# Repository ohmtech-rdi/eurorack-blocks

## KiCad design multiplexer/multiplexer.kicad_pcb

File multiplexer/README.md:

# multiplexer

## Description

This block allows to multiplex up to 8 `pot` or `trim` values into a single value.
Its design is detailed [here](./documentation/design.md).

## Overview

The number of actual Analog GPIOs on an MCU is always very limited, and one can quickly
have more controls and CVs on their panel than the number of available Analog GPIOs.

Multiplexing multiple signals to one signal allows to overcome this problem, at the expense
of a slower reading rate. Therefore it is suited for slowly varying signals such as the ones
delivered by a potentiometer.

This block provides up to 8 signals multiplexing. Reading a particular input is done
by putting the address of the input as a number expressed in binary.

Since 1 Analog GPIO is needed for the signal, 3 General GPIOs for the address, to reach a total
of 8 inputs, when a traditional MCU has far more General GPIOs than analog GPIOs.

Multiple `multiplexer` can be used, for example for a module with 8 parameters,
one `multiplexer` for the 8 `pot`, and another for the 8 attenuverter `trim`.
In that case, note that the same 3 GPIO outputs address can be reused for both multiplexers.

## Connecting

- This block needs its `GND` to be connected to the ground. All `GND` pins are connected
   internally,
- This block needs its `3V3A` to be connected to the Daisy Seed 3V3 Analog Power I/O on Pin 21,
- The signal `OUT` is the multiplexer output. It should be connected to any Analog GPIO of the
   target MCU. See [Daisy Seed pinout](https://images.squarespace-cdn.com/content/v1/58d03fdc1b10e3bf442567b8/1591827747342-HCXMM2NNR26SP5F4U2CJ/ke17ZwdGBToddI8pDm48kN5PbQBGNYbW-5Hm1pf8hRF7gQa3H78H3Y0txjaiv_0fDoOvxcdMmMKkDsyUqMSsMWxHk725yiiHCCLfrh8O1z4YTzHvnKhyp6Da-NYroOW3ZGjoBKy3azqku80C789l0kLp48N9LluBiCpBrPZntaz462IffsVrAff3VJkwKncM1HZuDnV98dfxM9yHlqFkUQ/DaisyPinoutRev4%404x.png?format=500w) for details.
- The signals from `IN0` to `IN7` are the inputs signals which would typically be connected to
   a `pot` or `trim` block `OUT`.

## Using

```c++
int main ()
{
   using namespace erb;
   
   Module module;
   Multiplexer mux (
      module, AdcPin6,              // 1.
      Pin23, Pin24, Pin25           // 2.
   );
   
   module.run ([&](){
      for (size_t i = 0 ; i < 8 ; ++i)
      {
         float pot_value = mux [i]; // 3.
      }
   });
}
```

1. Attach the multiplexer to the module and specify the same analog pin
   as the one used for connecting,
2. And specify the same digitals pins as the one used for connecting,
3. Retrieve the normalized (in the `0.f` to `1.f` range) floating-point pot value
   for input `IN` number `i`.

The `Multiplexer` class reference is available [here](./documentation/reference.md).

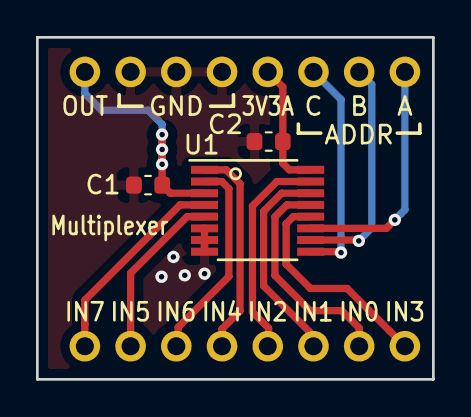
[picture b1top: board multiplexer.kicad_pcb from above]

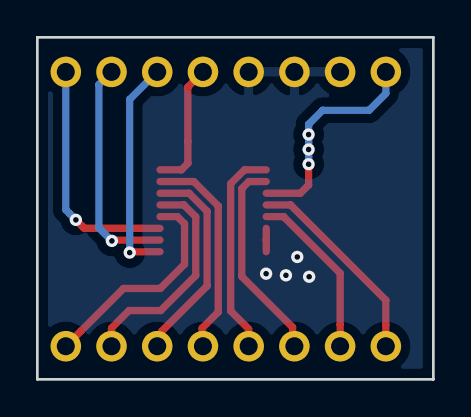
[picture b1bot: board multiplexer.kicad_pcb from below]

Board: 2 copper layers, 22.0 x 19.0 mm, 5 parts (2 on the bottom side), 14 nets.

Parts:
C1: 1n; C_0603_1608Metric
C2: 100n; C_0603_1608Metric
J2: BOTTOM; PinHeader_1x08_P2.54mm_Vertical
J3: TOP; PinHeader_1x08_P2.54mm_Vertical
U1: 4051; TSSOP-16_4.4x5mm_P0.65mm

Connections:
+3V3: C2.2, J3.5, U1.16
ADDR_0: J3.8, U1.11
ADDR_1: J3.7, U1.10
ADDR_2: J3.6, U1.9
GND: C1.2, C2.1, J3.2, J3.3, J3.4, U1.6, U1.7, U1.8
IN0: J2.7, U1.13
IN1: J2.6, U1.14
IN2: J2.5, U1.15
IN3: J2.8, U1.12
IN4: J2.4, U1.1
IN5: J2.2, U1.5
IN6: J2.3, U1.2
IN7: J2.1, U1.4
OUT: C1.1, J3.1, U1.3

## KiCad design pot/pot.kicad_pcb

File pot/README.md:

# pot

## Description

This block is a simple potentiometer.
Its design is detailed [here](./documentation/design.md).

## Connecting

- This block needs its `GND` to be connected to the ground. All `GND` pins are connected
   internally,
- This block needs its `3V3A` to be connected to the Daisy Seed 3V3 Analog Power I/O on Pin 21,
- The signal `OUT` is the potentiometer value. It should be connected to any Analog GPIO of the
   target MCU. See [Daisy Seed pinout](https://images.squarespace-cdn.com/content/v1/58d03fdc1b10e3bf442567b8/1591827747342-HCXMM2NNR26SP5F4U2CJ/ke17ZwdGBToddI8pDm48kN5PbQBGNYbW-5Hm1pf8hRF7gQa3H78H3Y0txjaiv_0fDoOvxcdMmMKkDsyUqMSsMWxHk725yiiHCCLfrh8O1z4YTzHvnKhyp6Da-NYroOW3ZGjoBKy3azqku80C789l0kLp48N9LluBiCpBrPZntaz462IffsVrAff3VJkwKncM1HZuDnV98dfxM9yHlqFkUQ/DaisyPinoutRev4%404x.png?format=500w) for details.

## Using

```c++
int main ()
{
   using namespace erb;

   Module module;
   Pot pot (module, AdcPin6); // 1.

   module.run ([&](){
      float pot_value = pot;  // 2.
   });
}
```

1. Attach the pot to the module and specify the same analog pin as the one used for connecting,
2. Retrieve the normalised (in the  `0.f` to `1.f` range) or bipolar (in the `-1.f` to `1.f` range)
   floating-point pot value.

The `Pot` class reference is available [here](./documentation/reference.md).

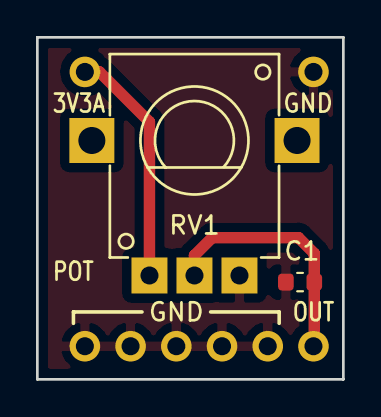
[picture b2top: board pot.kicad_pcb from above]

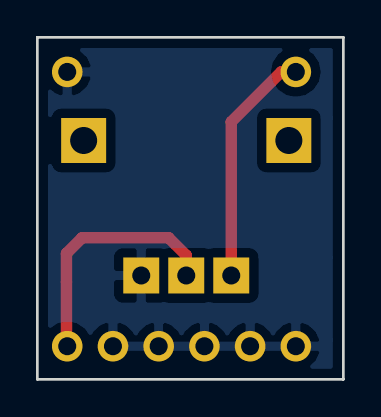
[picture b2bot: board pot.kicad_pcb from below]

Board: 2 copper layers, 17.0 x 19.0 mm, 5 parts (3 on the bottom side), 3 nets.

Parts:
C1: 100n; C_0603_1608Metric
J1: OUT; PinHeader_1x06_P2.54mm_Vertical
J2: GND; PinHeader_1x01_P2.54mm_Vertical
J3: 3V3; PinHeader_1x01_P2.54mm_Vertical
RV1: 100k; AlphaPot9ShaftD

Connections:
+3V3: J3.1, RV1.1
GND: C1.1, J1.2, J1.3, J1.4, J1.5, J1.6, J2.1, RV1.3
OUT: C1.2, J1.1, RV1.2

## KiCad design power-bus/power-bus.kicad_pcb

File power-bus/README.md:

# power-bus

## Description

This block is a simple eurorack power bus connector adapter.
It is protected against eurorack connector accidental polarity inversion.

It is adapted from the [Mutable Instuments Tides schematics](https://mutable-instruments.net/modules/tides/downloads/tides_v40.pdf).

## Usage

This block provides:
- The 3 standard `+12V`, `GND`, `–12V` lines, to typically power the audio op-amps,
   such as `audio-in-daisy` or `audio-out-daisy`,
- A rectified +12V line, named `+12R`, suitable for use with subsequent power regulators,
   such as `regulator-daisy`.

## Design

The `+12V` and `-12V` are protected against potential digital switching noise from other
eurorack modules in the system using ferrite beads.

In contrast, the `+12R` is only rectified against accidental polarity inversion, but not against
noise. It is expected that this line would be connected to a linear voltage regulator, such
as the one in `regulator-daisy`, which are very good at preventing noise to flow back
into the circuit.
The implicit star configuration is going to prevent that when prototyping with those blocks.
But care needs to be taken for return currents in the `GND` plane when designing the module
PCB.

> Gerber renders made with [tracespace view](https://tracespace.io/view/).

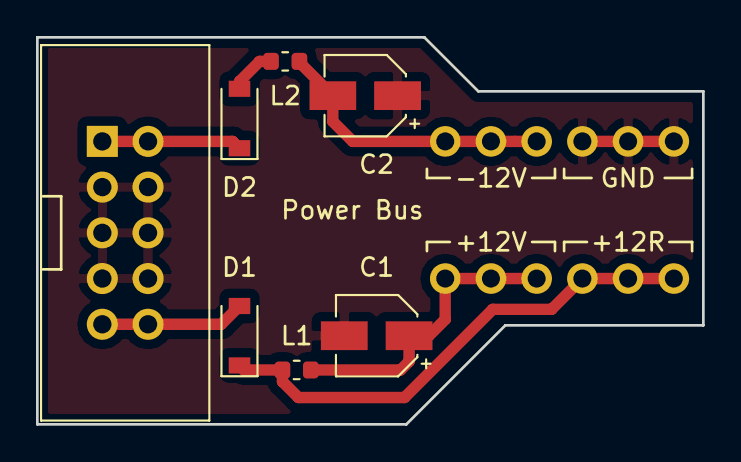
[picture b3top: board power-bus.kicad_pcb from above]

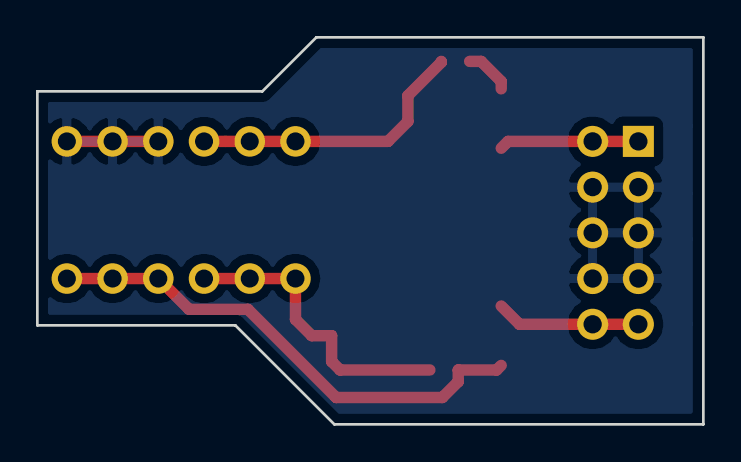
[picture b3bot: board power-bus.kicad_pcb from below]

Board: 2 copper layers, 37.0 x 21.5 mm, 9 parts (2 on the bottom side), 7 nets.

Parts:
C1, C2: 22u; CP_Elec_4x5.8
D1, D2: D_Schottky; D_SOD-123
J1: POWER BUS; IDC-Header_2x05_P2.54mm_Vertical
J2: POWER1; PinHeader_1x06_P2.54mm_Vertical
J3: POWER2; PinHeader_1x06_P2.54mm_Vertical
L1, L2: Ferrite_Bead; L_0603_1608Metric

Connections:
+12E: D1.2, J1.9, J1.10
+12R: D1.1, J2.4, J2.5, J2.6, L1.2
+12V: C1.1, J2.1, J2.2, J2.3, L1.1
-12E: D2.1, J1.1, J1.2
-12V: C2.2, J3.1, J3.2, J3.3, L2.1
GND: C1.2, C2.1, J1.3, J1.4, J1.5, J1.6, J1.7, J1.8, J3.4, J3.5, J3.6
unnamed: D2.2, L2.2

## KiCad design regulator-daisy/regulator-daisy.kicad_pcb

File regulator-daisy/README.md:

# regulator-daisy

## Description

This block is a simple voltage regulator aim to power the Daisy Seed.
Its design is detailed [here](./documentation/design.md).

## Connecting

- This block needs its `GND` to be connected to the ground. All `GND` pins are connected
   internally,
- This block needs its `+12R` to be connected to the `+12R` of the `power-bus`,
- The pin `+5VD` is the regulated output.
   It needs to be connected to the Daisy Seed `VIN` (Pin 39)
   See [Daisy Seed pinout](https://images.squarespace-cdn.com/content/v1/58d03fdc1b10e3bf442567b8/1591827747342-HCXMM2NNR26SP5F4U2CJ/ke17ZwdGBToddI8pDm48kN5PbQBGNYbW-5Hm1pf8hRF7gQa3H78H3Y0txjaiv_0fDoOvxcdMmMKkDsyUqMSsMWxHk725yiiHCCLfrh8O1z4YTzHvnKhyp6Da-NYroOW3ZGjoBKy3azqku80C789l0kLp48N9LluBiCpBrPZntaz462IffsVrAff3VJkwKncM1HZuDnV98dfxM9yHlqFkUQ/DaisyPinoutRev4%404x.png?format=500w) for details.

The Daisy Seed `DGND` (Pin 40) needs to be connected to `AGND` (Pin 20). Both needs to
be connected to `GND`.

> ⚠️ Not connecting `DGND` to `AGND` on the Daisy Seed [may **destroy it**](https://forum.electro-smith.com/t/externally-powering-the-seed/826) ⚠️

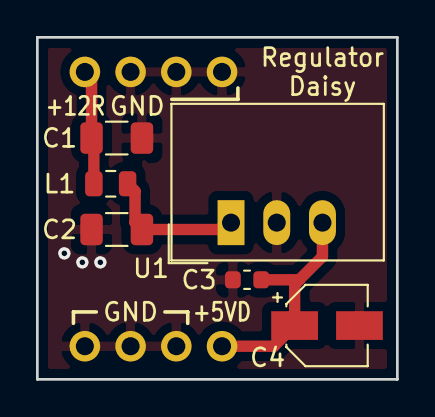
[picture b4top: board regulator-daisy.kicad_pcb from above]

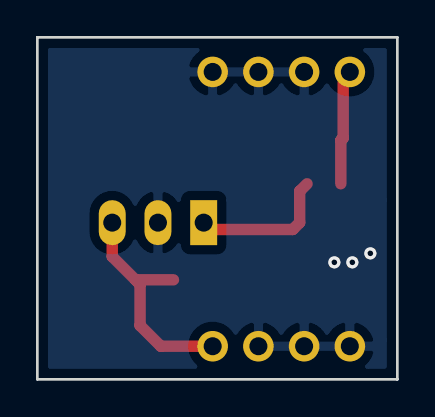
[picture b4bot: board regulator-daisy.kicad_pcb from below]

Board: 2 copper layers, 20.0 x 19.0 mm, 8 parts (2 on the bottom side), 4 nets.

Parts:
C1, C2: 22u; C_1206_3216Metric
C3: 100n; C_0603_1608Metric
C4: 10u; CP_Elec_4x5.8
J1: IN; PinHeader_1x04_P2.54mm_Vertical
J2: OUT; PinHeader_1x04_P2.54mm_Vertical
L1: 33u; L_0805_2012Metric
U1: R-78E5.0-0.5; Converter_DCDC_RECOM_R-78E-0.5_THT

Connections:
+5VD: C3.1, C4.1, J2.1, U1.3
+12R: C1.1, J1.1, L1.1
GND: C1.2, C2.2, C3.2, C4.2, J1.2, J1.3, J1.4, J2.2, J2.3, J2.4, U1.2
unnamed: C2.1, L1.2, U1.1
